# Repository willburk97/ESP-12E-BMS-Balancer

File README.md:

# ESP-12E-BMS-Balancer
li-ion BMS / Balancer made of multiple NodeMCU ESP-12E (one per cell) using Adafruit io to store/track/trend each cell's voltage.

I used an LM3671 from adafruit to power the 3.3v in of the ESP-12E directly because my NodeMCU version uses an LDO regulator which drops half 
a volt or so. I wanted my ESP-12E to be able to continue monitoring the cell all the way down to 2.4 volts or so. The LDO wouldn't allow that.

I used an IRFZ44 mosfet (driven by D1 through a resistor) to connect a 16 ohm / 3W resistor to the batery input.  At a ~4VDC input this'd be 250mA and 1W worth of drain.  
The code leads to a battery drain (mosfet) duty cycle of about 80%, so technically about 800mW of drain.  While draining, the resistor can be touched momentarily but is 
hot enough to burn you.  It was not hot enough to melt my temporary breadboard or the wires/components nearby.

As mentioned in the code, A0 on the NodeMCU has a built in voltage divider of 100k:220k ohms.  This enables you to simply jumper from A0 to the battery in with a 220k 
resistor (for li-ion) which creates a 100k:440k voltage divider, which is a ratio of 1:5.4 

In case the search function checks the readme for codewords, here're some:
NodeMCU, ESP12, ESP-12, ESP12E, ESP-12E, ESP8266, Battery Management System, Balance, lithium, pack

I added the code from an ESP32 I was testing as well.  I coded it to monitor battery4 (and the code would have to be adjusted to match the battery it is connected to.)
This code was used before I added the staleData code you'll see in the ESP12 code.  The side effect of not having the staleData code is that if a battery is low and then
disconnected from the internet, this ESP will attempt to drain it's battery down to that last known voltage...ignoring the fact that the last known voltage could be very
very old.  This is handy for testing and/or forcing a single cell to a certain voltage but not ideal for regular use or as a reliable BMS. (Basically, I think the staleData
code is important, I just never implemented it in the ESP32 code.)

Added Schematic and Board layouts for two different ESP-12E BMS styles. One with the LM3671 from Adafruit and one without.  It can be used without the Adafruit board, but
somewhere around 3.0v the ESP-12E will turn off because of the inherent voltage drop across the LDO voltage regulator. The 'Low Voltage' version uses the Adafruit buck
converter, the other does not.  

I haven NOT double checked the schematic for accuracy nor have I printed the PCB to test it out.  Please sanity check them both before use.
I used Autodesk Eagle for the schematic and board layout.

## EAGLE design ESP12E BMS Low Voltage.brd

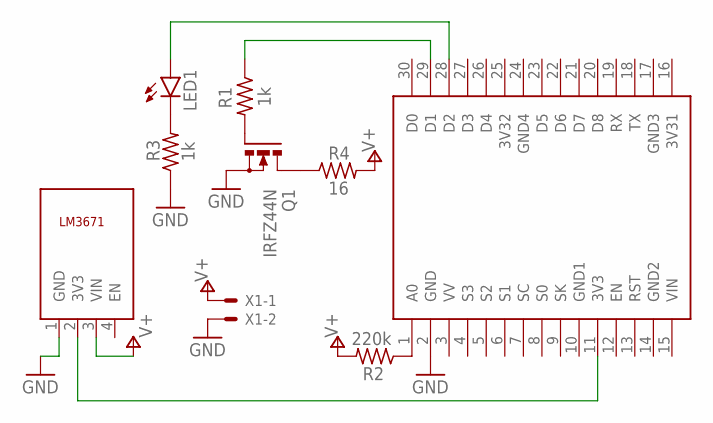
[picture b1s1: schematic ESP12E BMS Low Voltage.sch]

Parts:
LED1: TLLR4400; LED3MM
Q1: IRFZ44N; TO220BH
R1, R3: 1k; 0204/7
R2: 220k; 0204/7
R4: 16; P0613/15
U$1: NODEMCU
U$2: LM3671
X1: JST-XH-02-PIN-ROUND-PAD; JST-XH-02-PACKAGE-ROUND-PAD

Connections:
3V31: U$1.16 (3V31)
3V32: U$1.25 (3V32)
GND: Q1.S, R3.1, U$1.2 (GND), U$2.1 (GND), X1.2
GND1: U$1.10 (GND1)
GND2: U$1.14 (GND2)
GND3: U$1.17 (GND3)
GND4: U$1.24 (GND4)
unnamed: LED1.K (C), R3.2
unnamed: Q1.G, R1.2
unnamed: Q1.D, R4.1
unnamed: R1.1, U$1.29 (D1)
unnamed: LED1.A, U$1.28 (D2)
unnamed: R2.1, U$1.1 (A0)
unnamed: U$1.11 (3V3), U$2.2 (3V3)
V+: R2.2, R4.2, U$2.3 (VIN), X1.1

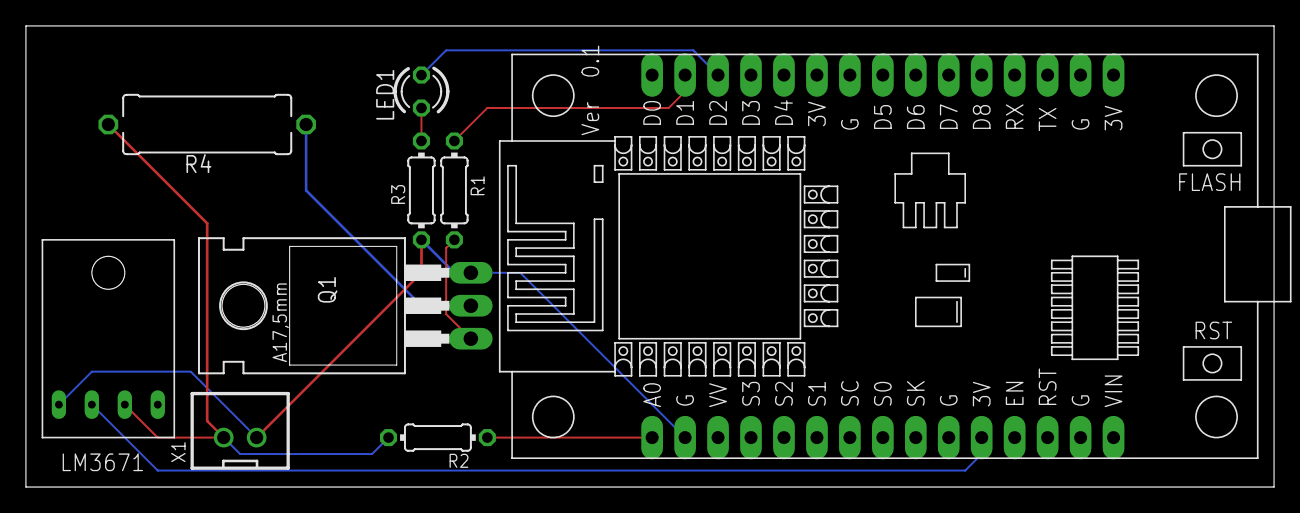
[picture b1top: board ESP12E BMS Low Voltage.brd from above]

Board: 2 copper layers, 96.2 x 35.5 mm, 9 parts (0 on the bottom side), 9 nets.

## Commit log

2020-07-26 Add files via upload
    Details are within the code. I hope to tweak the code so it's easier to configure for each cell. Currently, you'll have to change the code before you upload it to match the cell. (I.e. correct the co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
2020-07-26 Photos of functional breadboard
2020-07-26 Delete A5840F60-681C-4646-A060-AD3B15509CE3.jpeg
    Zoomed out version seems pointless.
2020-07-28 Add files via upload
    Adding draft ESP32 code.
2020-08-06 Update README.md
    Added notes about recently added schematics and boards.
